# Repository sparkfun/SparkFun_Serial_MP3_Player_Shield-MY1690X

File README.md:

SparkFun Serial MP3 Player Shield - MY1690X
========================================

[*SparkFun Serial MP3 Player Shield - MY1690X (DEV-28021)*](https://www.sparkfun.com/catalog/product/view/id/28021)

The SparkFun Serial MP3 Player Shield - MY1690X is an R3 Arduino shield built around the MY1690X audio decoder IC. The MY1691X supports both .WAV and .MP3 audio files stored on a connected microSD card with up to 32GB capacity and formatted to FAT16 or FAT32. The MY1690X communicates over serial UART so we designed this shield to allow users to control the MY1690X while mounted on a compatible Arduino development board with an R4 footprint. 

Repository Contents
-------------------

* **.github/workflows** - YAML files used for GitHub Actions and GitHub Pages/mkdocs
* **/Hardware** - KiCad design files (.kicad_pcb, .kicad_sch, .kicad_pro)
  * **/Production** - Production panel files (.kicad_pcb)
* **/docs** - Online documentation files
  * **/assets** - Folder containing all the file assets used for product documentation
    * **/board_files** - Copy of design files used for product documentation
    * **/component_documentation** - Datasheets and manuals for hardware components
    * **/img** - Images for product documentation
  * **/github** - Files stating how to contribute and filing issues used for product documentation
  * **/javascript** - Folder containing custom javascript used for product documentation
  * **/stylesheet** - Folder containing CSS files used for product documentation
* **/overrides** - Customization files used for product documentation
  * **/.icons** - Icons used for GitHub used for product documentation
  * **./partials** - Used for product documentation

Documentation
--------------

* **[Arduino Library](https://github.com/sparkfun/SparkFun_MY1690_MP3_Decoder_Arduino_Library/)** - Arduino Library for the SparkFun Serial MP3 Player Shield - MY1690X.
* **[Hookup Guide](https://docs.sparkfun.com/SparkFun_Serial_MP3_Player_Shield-MY1690X)** - Basic hookup guide for the SparkFun Serial MP3 Player Shield - MY1690X.

Product Versions
----------------
* [DEV-28021](https://www.sparkfun.com/catalog/product/view/id/28021) - v1.0

Version History
---------------
* v1.0 - Initial release

License Information
-------------------

This product is _**open source**_!

Please review the LICENSE.md file for license information.

If you have any questions or concerns on licensing, please contact technical support on our [SparkFun forums](https://community.sparkfun.com/c/community/general-chit-chat/37).

Distributed as-is; no warranty is given.

- Your friends at SparkFun.

_<COLLABORATION CREDIT>_

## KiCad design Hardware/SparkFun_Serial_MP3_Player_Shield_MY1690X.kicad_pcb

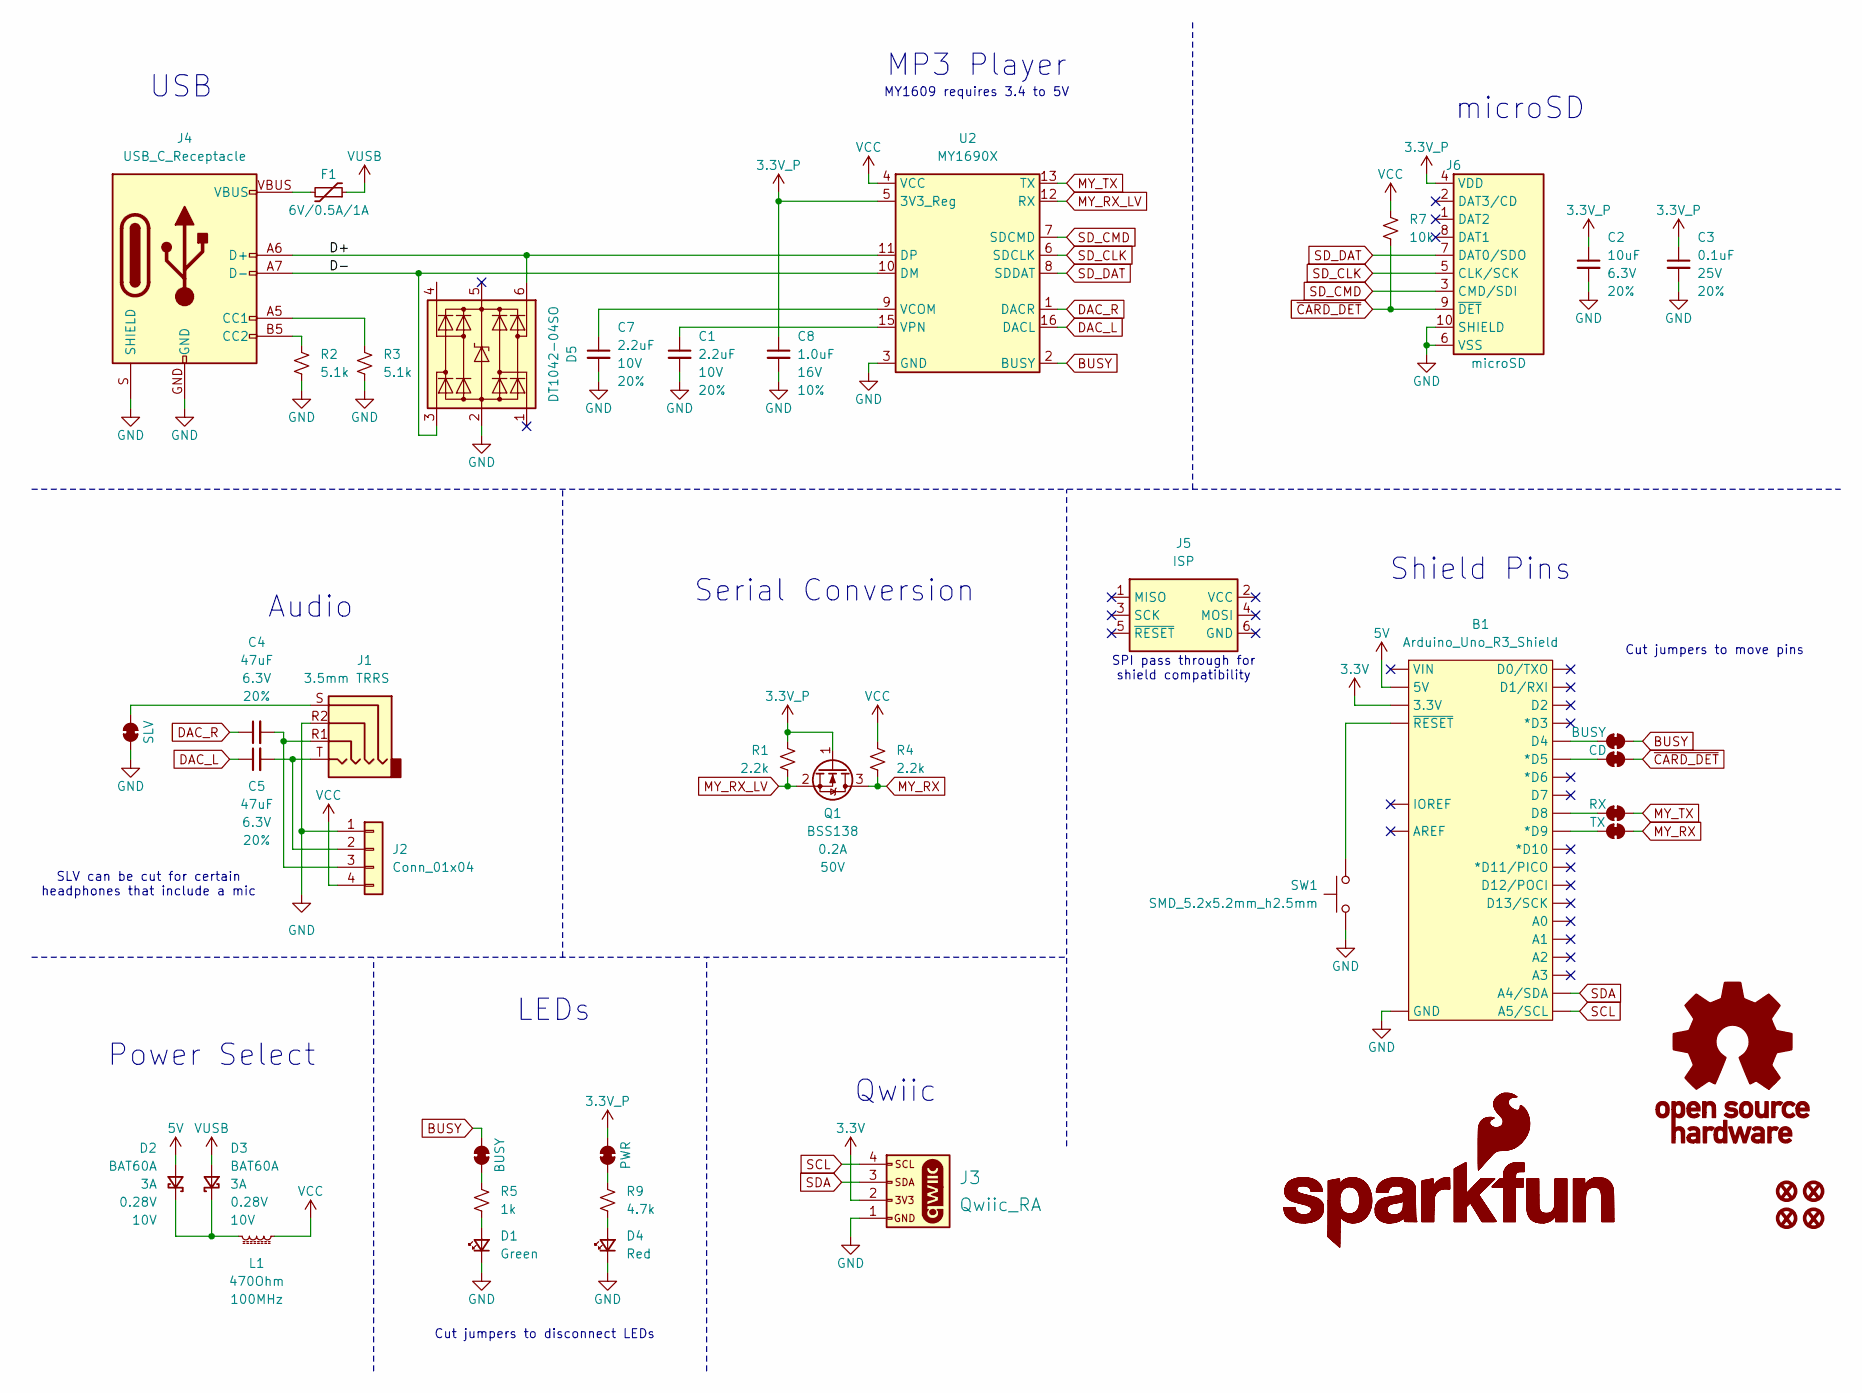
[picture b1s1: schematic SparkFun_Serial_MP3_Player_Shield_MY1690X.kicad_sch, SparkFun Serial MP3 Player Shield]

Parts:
B1: Arduino_Uno_R3_Shield; Uno_R3_Shield_NoLabels
C1, C7: 2.2uF; C_0603_1608Metric; Voltage 10V; Tolerance 20%
C2: 10uF; C_0603_1608Metric; Voltage 6.3V; Tolerance 20%
C3: 0.1uF; C_0603_1608Metric; Voltage 25V; Tolerance 20%
C4, C5: 47uF; C_0805_2012Metric; Voltage 6.3V; Tolerance 20%
C8: 1.0uF; C_0603_1608Metric; Voltage 16V; Tolerance 10%
D1: Green; LED_0603_1608Metric_Green
D2, D3: BAT60A; SOD-323
D4: Red; LED_0603_1608Metric_Red
D5: DT1042-04SO; SOT23-6
F1: 6V/0.5A/1A; 0805
FID1, FID2, FID3, FID4: Fiducial_0.5mm; Fiducial_0.5mm_Mask1mm
G1: OSHW_Logo; Creative_Commons_License
G3: SparkFun_Logo
G5: SparkFun_Logo; SparkFun_Logo_8mm
J1: 3.5mm TRRS; Audio_Jack_3.5mm_TRRS_SMD_RA
J2: Conn_01x04; 1x04
J3: Qwiic_RA; JST_SMD_1.0mm-4_Black
J4: USB_C_Receptacle; USB-C_16
J5: ISP; 2x03_NoSilk
J6: microSD; microSD_External_Pin
JP1: BUSY; Jumper_2_NC_Trace
JP2: PWR; Jumper_2_NC_Trace
JP3: CD; Jumper_2_PTH_SMD_Combo-NC
JP4: BUSY; Jumper_2_PTH_SMD_Combo-NC
JP5: RX; Jumper_2_PTH_SMD_Combo-NC
JP6: TX; Jumper_2_PTH_SMD_Combo-NC
JP7: SLV; Jumper_2_NC_Trace
L1: 470Ohm; C_0603_1608Metric
Q1: BSS138; SOT23-3
R1, R4: 2.2k; R_0603_1608Metric
R2, R3: 5.1k; R_0603_1608Metric
R5: 1k; R_0603_1608Metric
R7: 10k; R_0603_1608Metric
R9: 4.7k; R_0603_1608Metric
SW1: SMD_5.2x5.2mm_h2.5mm; Push_SMD_5.2x5.2mm_h2.5mm
U2: MY1690X; SO-16

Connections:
3.3V: B1.3.3V, J3.2
3.3V_P: C2.1, C3.1, C8.1, J6.4 (VDD), JP2.2 (B), Q1.1 (G), R1.2, U2.5 (3V3_Reg)
5V: B1.5V, D2.2 (A)
/D+: D5.6 (I/O4), J4.A6 (D+), J4.B6 (D+), U2.11 (DP)
/D-: D5.3 (I/O2), J4.A7 (D-), J4.B7 (D-), U2.10 (DM)
BUSY: JP1.2 (B), JP4.2 (B), U2.2 (BUSY)
DAC_L: C5.1, U2.16 (DACL)
DAC_R: C4.1, U2.1 (DACR)
GND: B1.GND, C1.2, C2.2, C3.2, C7.2, C8.2, D1.1 (K), D4.1 (K), D5.2 (GND), J1.R2, J2.1, J3.1, J4.GND, J4.S (SHIELD), J6.6 (VSS), J6.10 (SHIELD), JP7.1 (A), R2.2, R3.1, SW1.1, U2.3 (GND), U2.14 (GND)
MY_RX: JP6.2 (B), Q1.3 (D), R4.1
MY_RX_LV: Q1.2 (S), R1.1, U2.12 (RX)
MY_TX: JP5.2 (B), U2.13 (TX)
unnamed: B1.D5 (*D5), JP3.1 (A)
unnamed: B1.D9 (*D9), JP6.1 (A)
unnamed: B1.~{RESET}, SW1.2
unnamed: D1.2 (A), R5.1
unnamed: D2.1 (K), D3.1 (K), L1.2
unnamed: D4.2 (A), R9.1
unnamed: F1.2, J4.VBUS
unnamed: C5.2, J1.T, J2.2
unnamed: C4.2, J1.R1, J2.3
unnamed: J4.A5 (CC1), R3.2
unnamed: J4.B5 (CC2), R2.1
unnamed: JP1.1 (A), R5.2
unnamed: JP2.1 (A), R9.2
unnamed: B1.D4, JP4.1 (A)
unnamed: B1.D8, JP5.1 (A)
unnamed: J1.S, JP7.2 (B)
unnamed: C7.1, U2.9 (VCOM)
unnamed: C1.1, U2.15 (VPN)
SCL: B1.A5/SCL, J3.4
SDA: B1.A4/SDA, J3.3
SD_CLK: J6.5 (CLK/SCK), U2.6 (SDCLK)
SD_CMD: J6.3 (CMD/SDI), U2.7 (SDCMD)
SD_DAT: J6.7 (DAT0/SDO), U2.8 (SDDAT)
VCC: J2.4, L1.1, R4.2, R7.2, U2.4 (VCC)
VUSB: D3.2 (A), F1.1
~CARD_DET: J6.9 (~DET), JP3.2 (B), R7.1

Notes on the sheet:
Cut jumpers to disconnect LEDs
MY1609 requires 3.4 to 5V
Serial Conversion
Cut jumpers to move pins
Audio
USB
microSD
SPI pass through for shield compatibility
SLV can be cut for certain headphones that include a mic
MP3 Player
Qwiic
Power Select
Shield Pins
LEDs

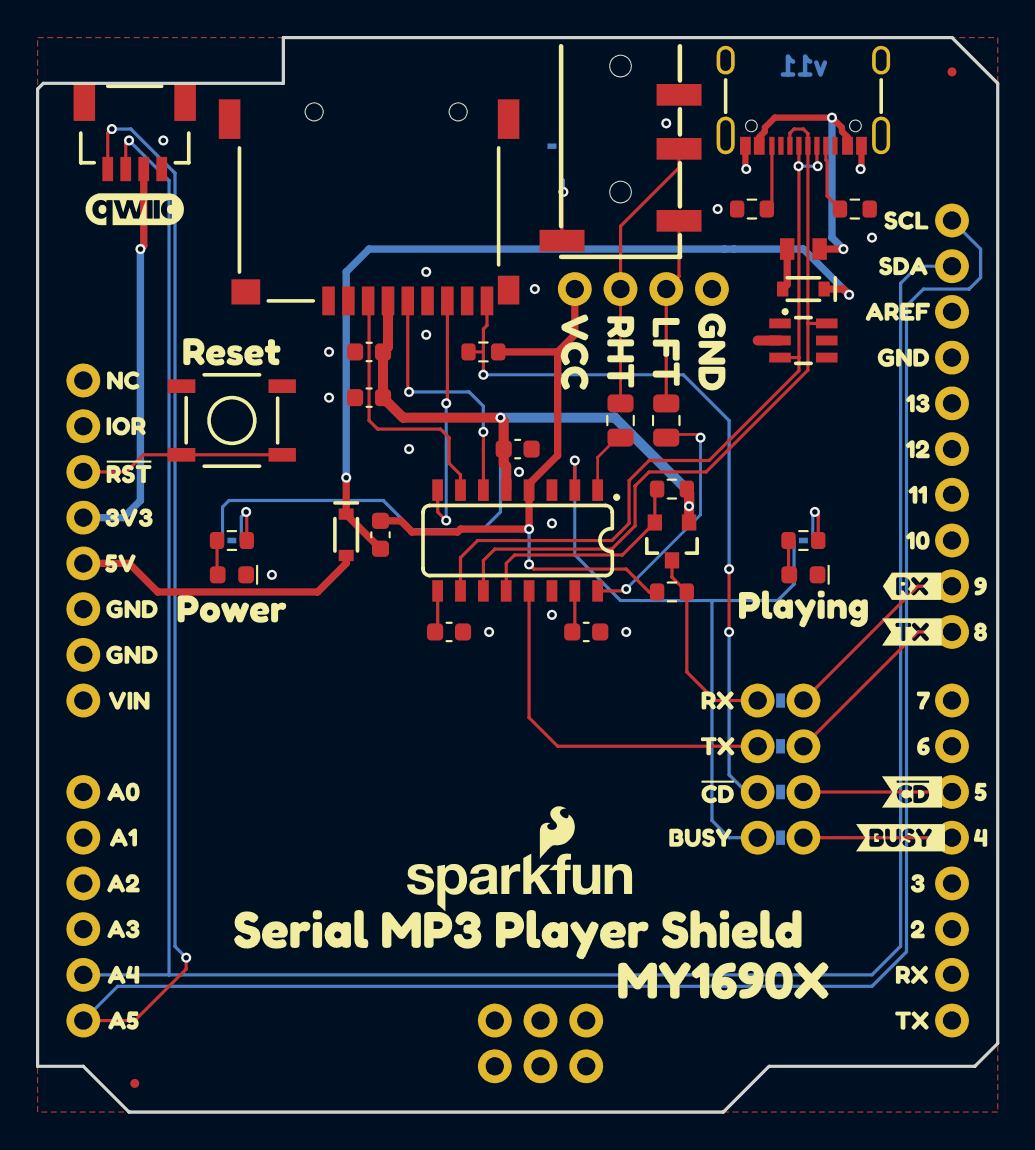
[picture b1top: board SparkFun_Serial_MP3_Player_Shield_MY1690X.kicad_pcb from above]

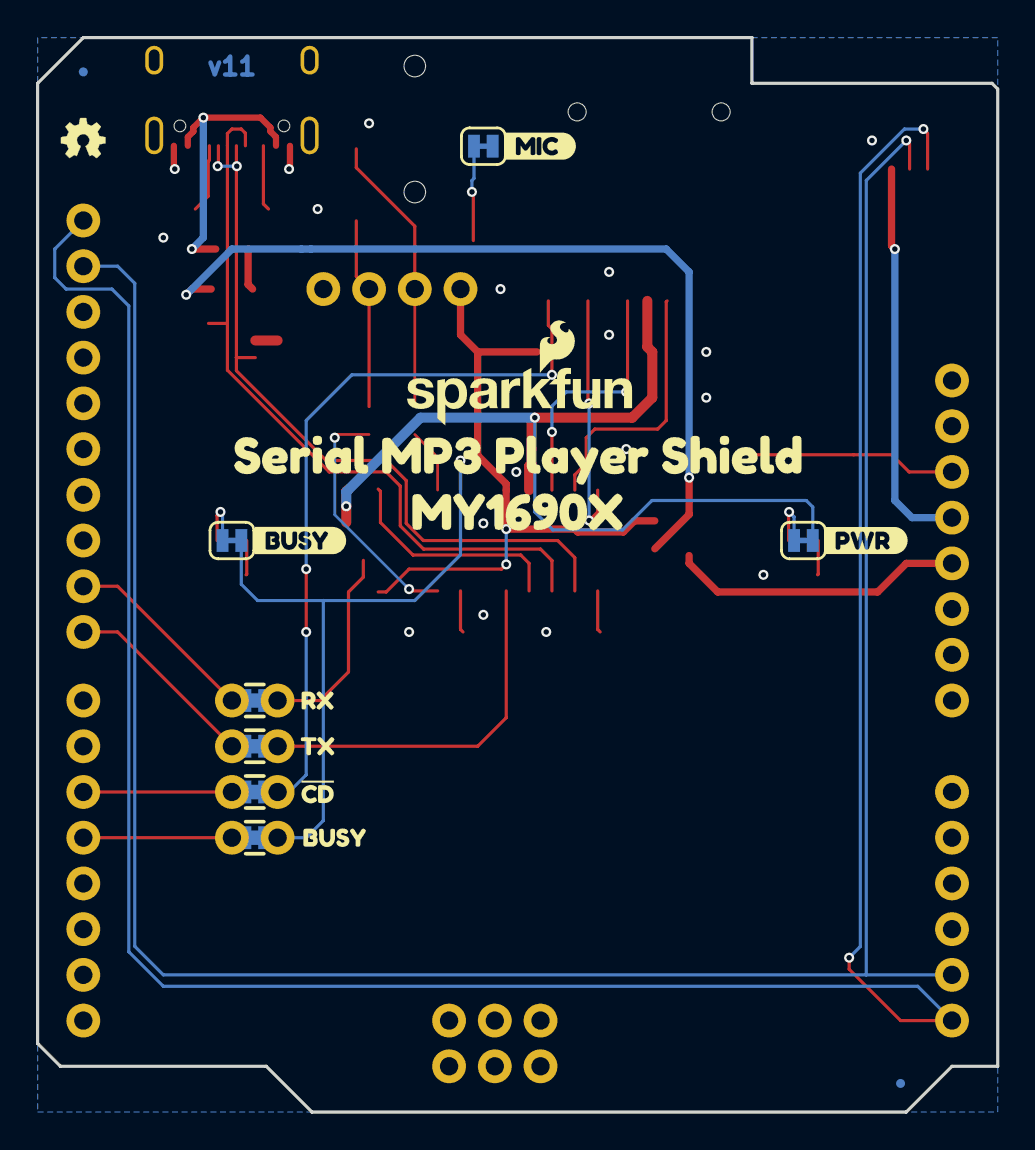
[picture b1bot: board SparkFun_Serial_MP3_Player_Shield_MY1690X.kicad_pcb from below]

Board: 2 copper layers, 53.3 x 59.7 mm, 102 parts (19 on the bottom side), 38 nets.

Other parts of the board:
Ref**: Val**; OSHW_Logo_2.5mm
kibuzzard-67A3E997, kibuzzard-67A3E997#2: G***; kibuzzard-67A3E997
kibuzzard-673AC551: G***; kibuzzard-673AC551
kibuzzard-673EA3A1: G***; kibuzzard-673EA3A1
kibuzzard-673EA43C: G***; kibuzzard-673EA43C
kibuzzard-673EA442: G***; kibuzzard-673EA442
kibuzzard-673EA447: G***; kibuzzard-673EA447
kibuzzard-673EA691: G***; kibuzzard-673EA691
kibuzzard-673EAACD, kibuzzard-673EAACD#2: G***; kibuzzard-673EAACD
kibuzzard-673EAE7C: G***; kibuzzard-673EAE7C
kibuzzard-673EAE8B: G***; kibuzzard-673EAE8B
kibuzzard-673EAE53: G***; kibuzzard-673EAE53
kibuzzard-673EAE60: G***; kibuzzard-673EAE60
kibuzzard-673EAEA7: G***; kibuzzard-673EAEA7
kibuzzard-673EAEB6: G***; kibuzzard-673EAEB6
kibuzzard-673EAEBB: G***; kibuzzard-673EAEBB
kibuzzard-673EAEC1: G***; kibuzzard-673EAEC1
kibuzzard-673EAEC8: G***; kibuzzard-673EAEC8
kibuzzard-673EAED1: G***; kibuzzard-673EAED1
kibuzzard-673EAEDE: G***; kibuzzard-673EAEDE
kibuzzard-673EAEE5: G***; kibuzzard-673EAEE5
kibuzzard-673EAF2D: G***; kibuzzard-673EAF2D
kibuzzard-673EAF5F: G***; kibuzzard-673EAF5F
kibuzzard-673EAF7B: G***; kibuzzard-673EAF7B
kibuzzard-673EAF7F: G***; kibuzzard-673EAF7F
kibuzzard-673EAF11: G***; kibuzzard-673EAF11
kibuzzard-673EAF23: G***; kibuzzard-673EAF23
kibuzzard-673EAF28: G***; kibuzzard-673EAF28
kibuzzard-673EAF33: G***; kibuzzard-673EAF33
kibuzzard-673EAF38: G***; kibuzzard-673EAF38
kibuzzard-673EAF45: G***; kibuzzard-673EAF45
kibuzzard-673EAF59: G***; kibuzzard-673EAF59
kibuzzard-673EAF71: G***; kibuzzard-673EAF71
kibuzzard-673EAF76: G***; kibuzzard-673EAF76
kibuzzard-673EAF83: G***; kibuzzard-673EAF83
kibuzzard-678AC9A2: G***; kibuzzard-678AC9A2
kibuzzard-678ACA35: G***; kibuzzard-678ACA35
kibuzzard-679D21EC: G***; kibuzzard-679D21EC
kibuzzard-679D21F4: G***; kibuzzard-679D21F4
kibuzzard-679D21F8: G***; kibuzzard-679D21F8
kibuzzard-679D21FD: G***; kibuzzard-679D21FD
kibuzzard-679D221C: G***; kibuzzard-679D221C
kibuzzard-679D222D: G***; kibuzzard-679D222D
kibuzzard-679D2133: G***; kibuzzard-679D2133
kibuzzard-679D2139: G***; kibuzzard-679D2139
kibuzzard-679D2221: G***; kibuzzard-679D2221
kibuzzard-679D2231: G***; kibuzzard-679D2231
kibuzzard-6792AB76: G***; kibuzzard-6792AB76
kibuzzard-6792AB99: G***; kibuzzard-6792AB99
kibuzzard-6792ACFA, kibuzzard-6792ACFA#2: G***; kibuzzard-6792ACFA
kibuzzard-6792ACFE, kibuzzard-6792ACFE#2: G***; kibuzzard-6792ACFE
kibuzzard-6792AD08, kibuzzard-6792AD08#2: G***; kibuzzard-6792AD08
kibuzzard-6792AD10, kibuzzard-6792AD10#2: G***; kibuzzard-6792AD10

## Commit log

2025-01-23 Add Busy LED, inline caps to TRRS, card detect, and power filtering.
2025-01-23 Remove examples (find them in the library)
2025-01-27 Fix PROD ID on TRRS
2025-01-27 Add panel
2025-02-02 Add README.MD
2025-02-03 Post review updates.
2025-02-05 Add panel files
2025-02-13 Updated top paste layer
2025-02-26 Add Board Dimensions to Measures Layer
2025-03-12 Add examples
2025-03-12 Change Playing resistor to 330
2025-04-07 Documentation
    Initial docs commit to add docs content & GH pages setup files/folders.
2025-04-09 Adding build workflows
    Adding build_documentation.yml for GH pages build.
2025-04-09 Deployed 63de6cc with MkDocs version: 1.6.1
2025-04-09 Update README.md
    Adding banner image & updating links.
2025-04-09 Deployed 0fa49ac with MkDocs version: 1.6.1
2025-04-15 Docs update
    Adding missing logo & thumbnail files & fixing copy/paste errors in contribute.md & file_issue.md.
2025-04-15 Deployed 2c552c1 with MkDocs version: 1.6.1

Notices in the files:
parts and their libraries:
https://creativecommons.org/licenses/by-sa/4.0
Released under the Creative Commons Attribution Share-Alike 4.0 License
